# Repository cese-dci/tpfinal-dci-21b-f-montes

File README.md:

## Trabajo práctico final de la asignatura DCI ##
Este repositorio contiene el trabajo práctico final para la asignatura de Diseño de Circuitos Impresos de la carrera de posgrado de FIUBA.

* Autor: FEDERICO MONTES DE OCA
* Título corto del trabajo: REPLICA ESP32-PICO-KIT
* Descripción:  Circuito Impreso Replica de Modulo ESP32-PICO-KIT

## Licencia de este trabajo ##
Licencia OHL. Para detalles ver https://ohwr.org/cernohl

## Estructura del Repo ##

El repo cuenta con tres directorios principales donde encontraremos lo siguiente:

* doc: Toda la información sobre el circuito, principalmente propia:
  * Documnetacion de trabajo del autor
* info: Toda la iformación recolectada, principalmente de terceros:
  * Esquematicos provistos por el fabricante
  * BOM provista por el fabricante
  * PCB provistos por el fabricante
  * Info en internet
* pcb: Archivos de diseño esquemático y pcb propios.

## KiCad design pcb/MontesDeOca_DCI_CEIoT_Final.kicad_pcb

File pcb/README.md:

## Archivos Kicad ##

En este directorio se incluyen:

* Archivos de proyecto.
* Esquemático.
* PCB.
* Modelos  3D.
* Bibliotecas de símbolos y huellas externas.

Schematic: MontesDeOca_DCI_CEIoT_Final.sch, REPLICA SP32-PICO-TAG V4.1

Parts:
ANT1: Proant440; ANT_PRO-OB-440
C1, C2: 10uF/25V(10%); C_0805_2012Metric
C3, C4, C6, C8, C9, C10: 0.1uF/25V(10%); C_0805_2012Metric
C5: 2.7pF/25V(+/-0.5pF); C_0805_2012Metric
C7: 1.6nH+/-0.3nH; C_0805_2012Metric
D1: RED LED; LED_0805_2012Metric
D2, D3, D4: LESD5D5.OCT1G; D_SOD-523
D5: BAT760-7; D_SOD-523
FID1, FID2, FID3: Fiducial; Fiducial_0.5mm_Mask1.5mm
J1: USB CON8; USB_A_Wuerth_61400826021_Horizontal_Stacked; Manufacturer Part # DX4R005JJ2R1800
J2, J3: Conn_01x20_MountingPin; PinHeader_1x20_P2.54mm_Vertical
L1: 4,7pF/25V(+/-0.5pF); C_0805_2012Metric
Q1, Q2: S8050(NPN); SOT-23
R1, R13: 2K(1%); R_0805_2012Metric
R2, R3: 0R(1%); R_0805_2012Metric
R4, R5: 1K(1%); R_0805_2012Metric
R6, R7: 0R(1%)(NC); R_0805_2012Metric
R8, R9, R15: 10K(1%); R_0805_2012Metric
R10, R14: 22.1K(1%); R_0805_2012Metric
R11: 47.5K(1%); R_0805_2012Metric
R12: 10K(1%)(NC); R_0805_2012Metric
R16: 10K(5%)(NC); R_0805_2012Metric
R17, R18: OR(1%); R_0805_2012Metric
SW1, SW2: SW_MEC_5G; SW_MEC_5GSH9
U1: AMS1117; SOT-223
U2: CP2102N; QFN-28-1EP_5x5mm_P0.5mm_EP3.35x3.35mm
U3: ESP32_SIP; QFN-48-1EP_7x7mm_P0.5mm_EP5.3x5.3mm

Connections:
+3.3VDAC: C2.1, C3.1, J2.20, J3.18, R13.2, R14.2, R16.2, U1.2 (VOUT), U1.4 (TAB), U2.6 (VDD), U2.7 (REGIN)
+3V3: C6.1, C8.1, R14.1, R15.2, U3.1 (VDDA), U3.3 (VDD3P3), U3.4 (VDD3P3), U3.19 (VDD3P3_RTC), U3.37 (VDD3P3_CPU), U3.43 (VDDA), U3.46 (VDDA)
+5V: C1.1, D5.1 (K), J3.20, R1.1, R10.1, U1.3 (VIN)
DTR: Q2.3 (E), R8.1, U2.28 (DTR)
EN: J2.18, Q1.2 (C), R18.1
FLASH_CLK: J2.3, U3.31 (SD_CLK(FLASH_CLK))
FLASH_CS: J3.1, U3.25 (IO16(FLASH_CS))
FLASH_SD0: J3.2, U3.27 (IO17(FLASH_SDO))
FLASH_SD1: J2.1, U3.33 (SD_DATA_1(FLASH_SD1))
FLASH_SD2: J3.3, U3.30 (SD_CMD(FLASH_SD2))
FLASH_SD3: J2.2, U3.32 (SD_DATA_0(FLASH_SD3))
GND: ANT1.1, C1.2, C2.2, C3.2, C4.2, C5.2, C6.2, C7.2, C8.2, C9.2, C10.2, D1.1 (K), D2.2 (A2), D3.2 (A2), D4.2 (A2), J1.5 (GND), J1.6 (GND), J1.7 (GND), J1.8 (GND), J1.9 (GND), J2.19, J3.19, R11.2, R12.2, SW1.1 (A), SW1.2 (A), SW2.1 (A), SW2.2 (A), U1.1 (GND), U2.3 (GND), U2.29 (PGND), U3.49 (GND)
IO0: J3.17, U3.23 (GPIO0)
IO2: J3.15, U3.22 (GPIO02)
IO4: J3.16, U3.24 (GPIO4)
IO5: J2.9, U3.34 (GPIO5)
IO9: J2.11, U3.28 (SD_DATA_2/IO9)
IO10: J2.10, U3.29 (SD_DATA_3/IO10)
IO12: J3.12, R16.1, U3.18 (MTDI)
IO13: J3.13, R6.1, U3.20 (MTCK)
IO14: J3.11, U3.17 (MTMS)
IO15: J3.14, R7.1, U3.21 (MTDO)
IO18: J2.8, U3.35 (GPIO18)
IO19: J2.6, U3.38 (GPIO19)
IO21: J2.4, U3.42 (GPIO21)
IO22: J2.5, U3.39 (GPIO22)
IO23: J2.7, U3.36 (GPIO23)
IO25: J3.6, U3.14 (GPIO25)
IO26: J3.7, U3.15 (GPIO26)
IO27: J3.10, U3.16 (GPIO27)
IO32: J3.8, U3.12 (32K_XP)
IO33: J3.9, U3.13 (32K_XN)
IO34: J2.15, U3.10 (VDET_1)
IO35: J2.14, U3.11 (VDET_2)
IO37: J2.17, U3.6 (SENSOR_CAPP)
IO38: J2.16, U3.7 (SENSOR_CAPN)
unnamed: ANT1.2, C5.1, L1.1
unnamed: C4.1, R15.1, U3.9 (CHIP_PU)
unnamed: C7.1, L1.2, U3.2 (LNA_IN)
unnamed: C9.1, R17.2, SW1.3 (B), SW1.4 (B)
unnamed: C10.1, R18.2, SW2.3 (B), SW2.4 (B)
unnamed: D1.2 (A), R1.2
unnamed: D2.1 (A1), D5.2 (A), J1.1 (VBUS)
unnamed: D3.1 (A1), J1.2 (D-), R2.1
unnamed: D4.1 (A1), J1.3 (D+), R3.1
unnamed: Q1.1 (B), R8.2
unnamed: Q2.1 (B), R9.2
unnamed: Q2.2 (C), R17.1
unnamed: R4.2, U2.25 (RXD)
unnamed: R5.2, U2.26 (TXD)
unnamed: R7.2, U2.23 (CTS)
unnamed: R10.2, R11.1, U2.8 (VBUS)
unnamed: R12.1, U2.11 (~SUSPENDb)
unnamed: R13.1, U2.9 (~RST)
RTS: Q1.3 (E), R6.2, R9.1, U2.24 (RTS)
RXD0: J2.12, R5.1, U3.40 (U0RXD)
SENSOR_VN: J3.5, U3.8 (SENSOR_VN)
SENSOR_VP: J3.4, U3.5 (SENSOR_VP)
TXD0: J2.13, R4.1, U3.41 (U0TXD)
USB_DN: R2.2, U2.4 (D+)
USB_DP: R3.2, U2.5 (D-)

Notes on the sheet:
Auto program DTR RTS—>EN IO0 1 1 1 1 0 0 1 1 1 0 0 1 0 1 1 0
Power Supply
ESP32 SIP
Micro USB 5V&USB-UART
Switch Buttons
Connectors

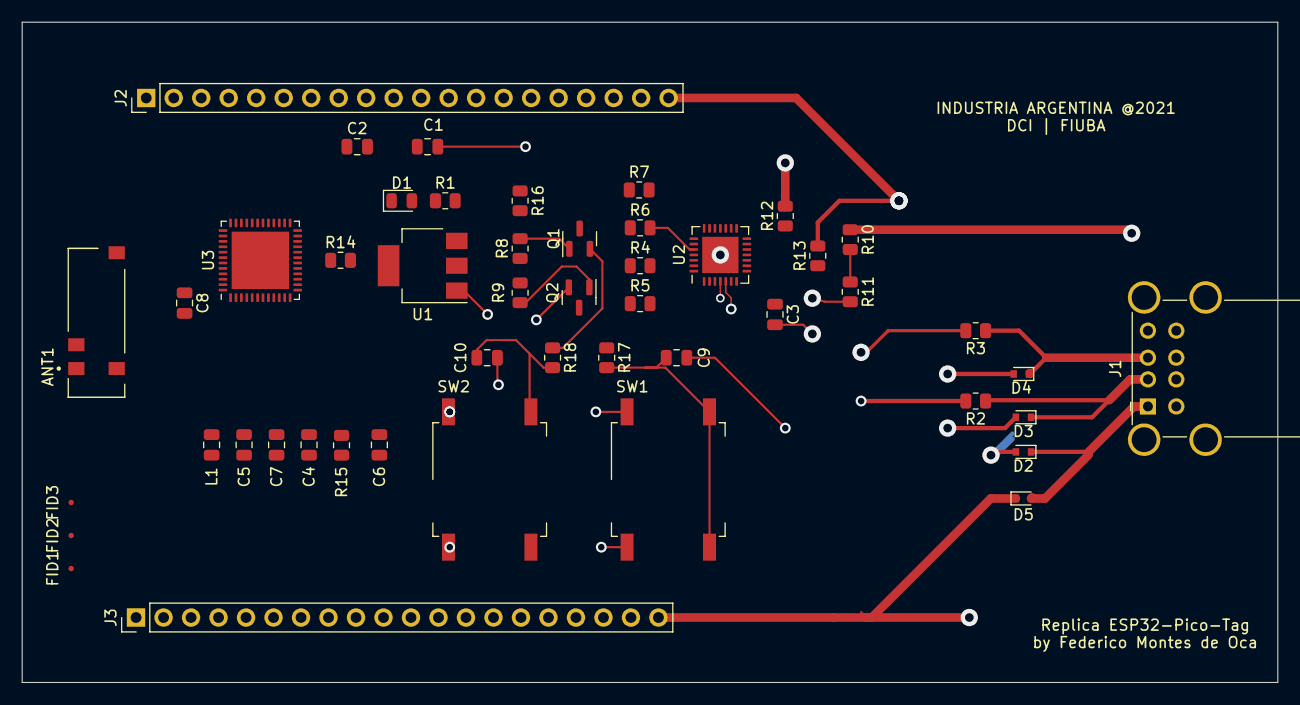
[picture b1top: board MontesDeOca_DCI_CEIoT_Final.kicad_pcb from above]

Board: 4 copper layers, 116.0 x 61.0 mm, 48 parts (0 on the bottom side), 61 nets.

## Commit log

2021-09-04 Update README.md
    Actualizacion de los terminos de licenciamiento
2021-09-04 Update README.md
    Actualizacion
2021-09-06 Actualizacion segun correcciones ralizadas
    Se avanzo adicionalmente en el posicionamiento de los componentes, el ruteo y el modelo 3D
2021-09-06 Actualizacion
